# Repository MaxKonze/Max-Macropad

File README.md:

# Max Macropad
I wanted to create a small Keyboard with shortcuts, so I can simplify a lot of tasks on my PC. For example it significantly simplifies Photoshop workflows by binding complex multi-key shortcuts to a single press on my Macropad.
Moreover I have always wanted to dive into electronics and this macropad was the perfect starting point for me. 

My Hackpad has 7 keys. 6 of those keys are macros oriented in a row2col matrix, while the 7th key is to change between two layers. I also used a rotary encoder with a switch to change the volume on my pc.

## Features:
- 7 Keys + a switch in the rotary encoder
- 1 rotary encoder
- 2 LEDs as status lights
- XIAO RP2040

## Challenges:
I had some difficulties routing my PCB, because I did this for the first time. After multiple iterations I was eventually satisfied with the result. Fusion went pretty smooth for me, because I already had a bit of Experience in 3D Modeling.

# The build process:
## PCB:
The PCB was designed in KiCAD. I used a matrix for the keys. For the 8th key I used the switch of the rotary encoder. My routing on the PCB is still a bit messy, but I already improved significantly, considering my first iteration of routing.

_Note: First I used the wrong LEDs (SK6812), but I changed them later on to the SK6812MINI-E_

## Case:
The case was made using Fusion. The top part of the case gets secured using M3 Screws and M3 heatset inserts. I decided to add a window to see the diodes, to give the design a bit more character. In the end I added a few design elements on the top side of my Hackpad, because I think it looks quite cool.

## Firmware:
I wrote the firmware using the KMK library in python. I'm using a 2-layer system to have more hotkeys on my macropad without needing more physical switches. For now I'm not 100% sure which hotkeys I want to have on my Hackpad, so I used letters as placeholders. I'll change that later. The LEDs work as a status light to show which layer is currently active.

[My Firmware](https://github.com/MaxKonze/Max-Macropad/blob/main/firmware/main.py)

# BOM:
|Amount|Part|
|------|---------
| 1x |XIAO RP2040 (with pins, so I can solder it through-hole)|
| 7x |Cherry MX Switches|
| 1x |EC11 Rotary Encoder EC11 + Switch + Vertical H20mm MountingHoles & 1x Knob|
| 7x |DSA Keycaps|
| 8x |1N4148 Diodes|
| 2x |SK6812 MINI-E LEDs|
| 7x |M3 Screws|
| 7x |M3 heat inserts|
| 1x |3D Printed Case|

(I used 3 more screws and heat inserts than allowed the secure my pcb in place. If it is not possible to ship those, I will just order them by myself.)

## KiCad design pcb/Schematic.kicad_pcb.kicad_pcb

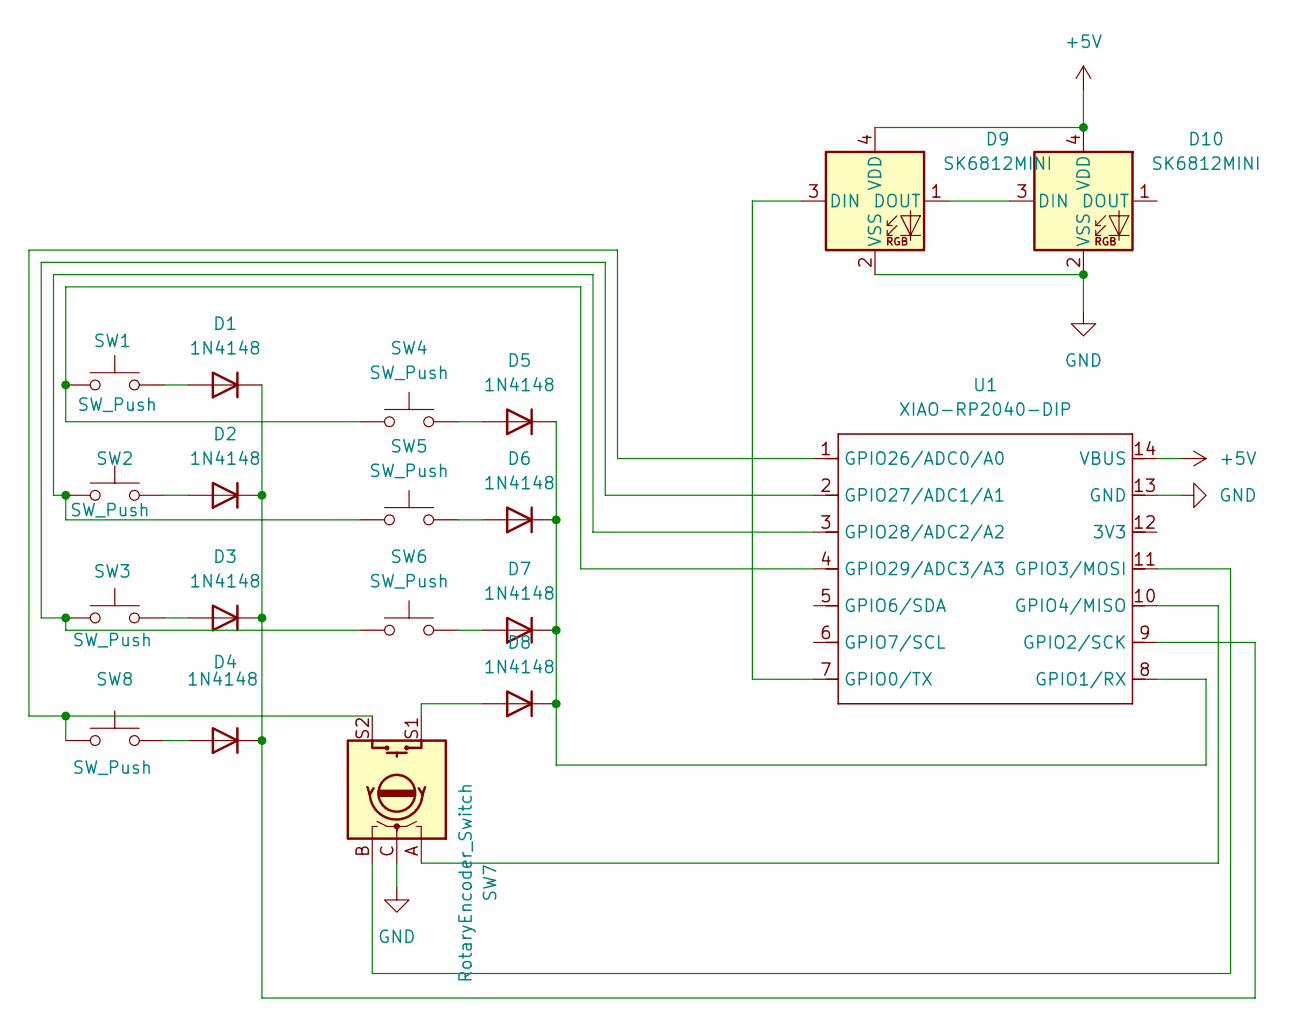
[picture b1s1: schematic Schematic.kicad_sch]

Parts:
D1, D2, D3, D4, D5, D6, D7, D8: 1N4148; D_DO-35_SOD27_P7.62mm_Horizontal
D9, D10: SK6812MINI; MX_SK6812MINI-E_REV
SW1, SW2, SW3, SW4, SW5, SW6, SW8: SW_Push; SW_Cherry_MX_1.00u_PCB
SW7: RotaryEncoder_Switch; RotaryEncoder_Alps_EC11E-Switch_Vertical_H20mm_MountingHoles
U1: XIAO-RP2040-DIP

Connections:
+5V: D9.4 (VDD), D10.4 (VDD), U1.14 (VBUS)
GND: D9.2 (VSS), D10.2 (VSS), SW7.C, U1.13 (GND)
unnamed: D1.2 (A), SW1.2
unnamed: D1.1 (K), D2.1 (K), D3.1 (K), D4.1 (K), U1.9 (GPIO2/SCK)
unnamed: D2.2 (A), SW2.2
unnamed: D3.2 (A), SW3.2
unnamed: D4.2 (A), SW8.2
unnamed: D5.2 (A), SW4.2
unnamed: D5.1 (K), D6.1 (K), D7.1 (K), D8.1 (K), U1.8 (GPIO1/RX)
unnamed: D6.2 (A), SW5.2
unnamed: D7.2 (A), SW6.2
unnamed: D8.2 (A), SW7.S1
unnamed: D9.3 (DIN), U1.7 (GPIO0/TX)
unnamed: D9.1 (DOUT), D10.3 (DIN)
unnamed: SW7.B, U1.11 (GPIO3/MOSI)
unnamed: SW7.A, U1.10 (GPIO4/MISO)
unnamed: SW7.S2, SW8.1, U1.1 (GPIO26/ADC0/A0)
unnamed: SW3.1, SW6.1, U1.2 (GPIO27/ADC1/A1)
unnamed: SW2.1, SW5.1, U1.3 (GPIO28/ADC2/A2)
unnamed: SW1.1, SW4.1, U1.4 (GPIO29/ADC3/A3)

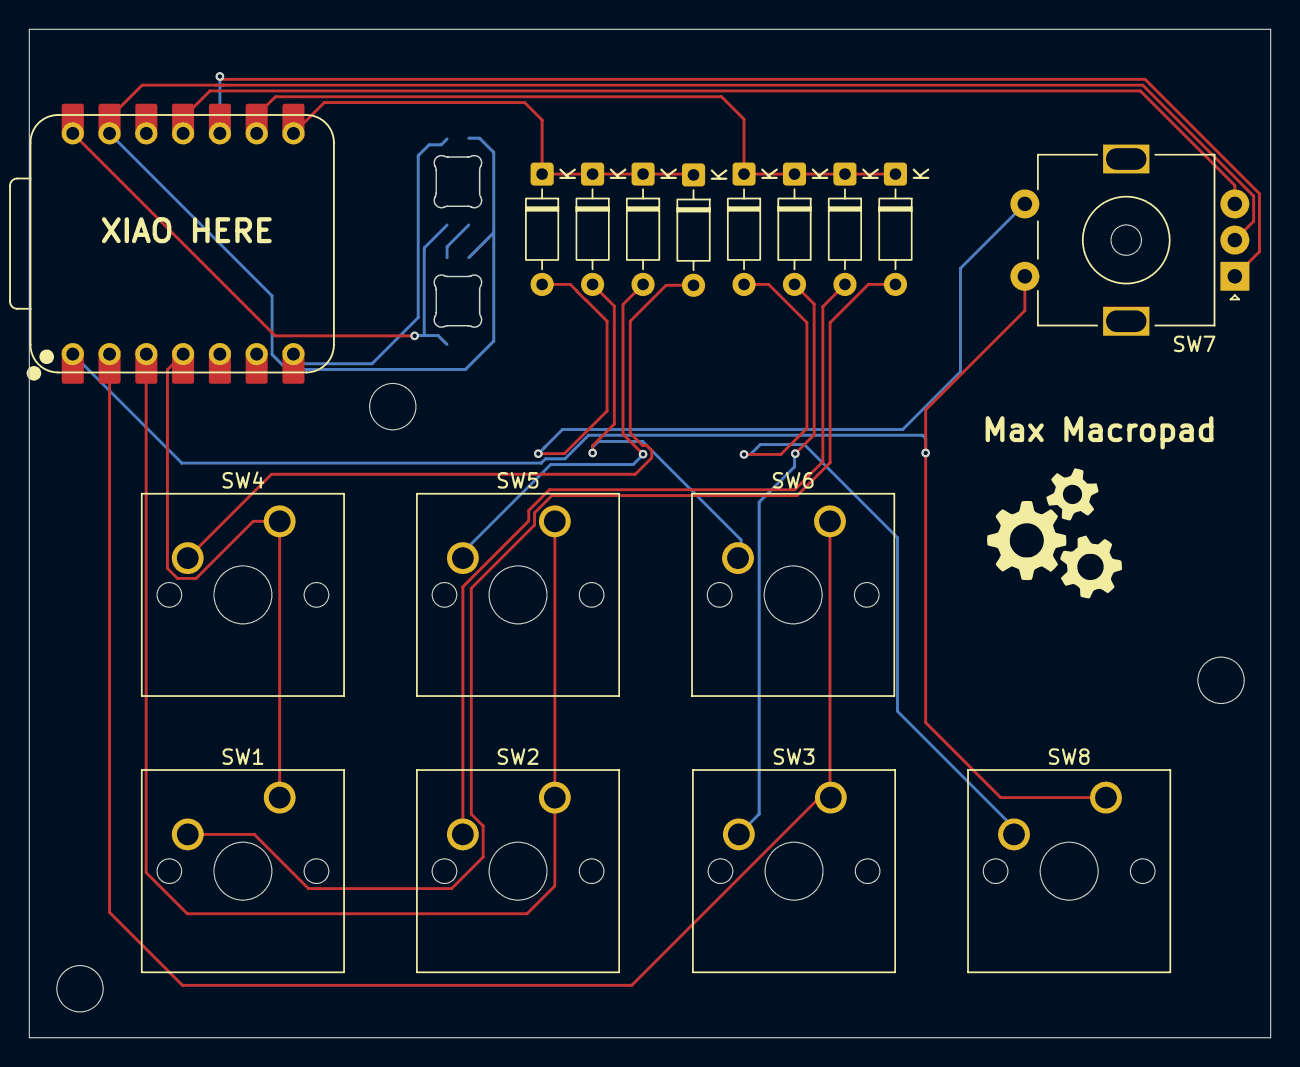
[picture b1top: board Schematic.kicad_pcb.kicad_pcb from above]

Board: 2 copper layers, 85.7 x 69.6 mm, 19 parts (0 on the bottom side), 20 nets.

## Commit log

2026-01-29 init commit
2026-01-29 Update README with project details and features
    Added description and features of the Max-Macropad.
2026-01-29 test
2026-01-30 Revise README with additional details and corrections
    Updated the README to correct the XIAO model and added sections on challenges, build process, and BOM.
2026-01-30 Update BOM description for XIAO RP2040
    Clarified BOM item for XIAO RP2040 to specify through-hole soldering.
2026-01-30 Update BOM with specific keycap and component details
2026-01-30 Update Hackpad description for key layout clarity
    Clarify the description of the Hackpad's key layout.
2026-02-11 new version
2026-02-11 Revise README for Max Hackpad
    Updated README with new title and additional design elements.
2026-02-11 Update README with note on additional hardware
    Added note about additional screws and heat inserts used.
2026-02-11 Edit README for grammar and clarity improvements
    Corrected minor grammatical errors and improved clarity in the README.
2026-02-11 Update README with corrections and enhancements
    Corrected minor typos and improved clarity in the README.
2026-02-11 Enhance README with case and firmware details
    Added images and improved case and firmware descriptions.
2026-02-11 prod files
2026-02-11 Adjust quantities of M3 screws and heat inserts
    Updated the quantity of M3 screws and heat inserts in the list.
2026-02-13 Fix typos and enhance readability in README.md
    Corrected typos and improved clarity in the README.
2026-02-13 Fix grammar and clarity in README.md
2026-02-13 Revise PCB section for clarity and grammar
    Corrected grammar and improved clarity in PCB description.
2026-02-13 Rename project from Hackpad to Macropad
    Updated project name from 'Max Hackpad' to 'Max Macropad'.
2026-02-13 new gerber
2026-02-20 new gerbers
2026-02-20 new image
2026-02-20 Update README to remove key orientation note
    Removed note about key orientation issue in Fusion.
2026-02-20 rm gerbers
2026-02-20 rename
2026-02-27 Enhance README with project details and BOM table
    Expanded the description of the Max Macropad project and formatted the BOM section into a table for better readability.
2026-02-28 new leds
2026-02-28 new files
2026-03-01 Correct status lights description and add LED note
    Updated README to reflect changes in status lights and added a note about LED revisions.
2026-03-03 new pcb (clean up)
2026-03-03 new gerbers (pcb clean up)
2026-03-03 file rename
2026-04-27 New firmware
